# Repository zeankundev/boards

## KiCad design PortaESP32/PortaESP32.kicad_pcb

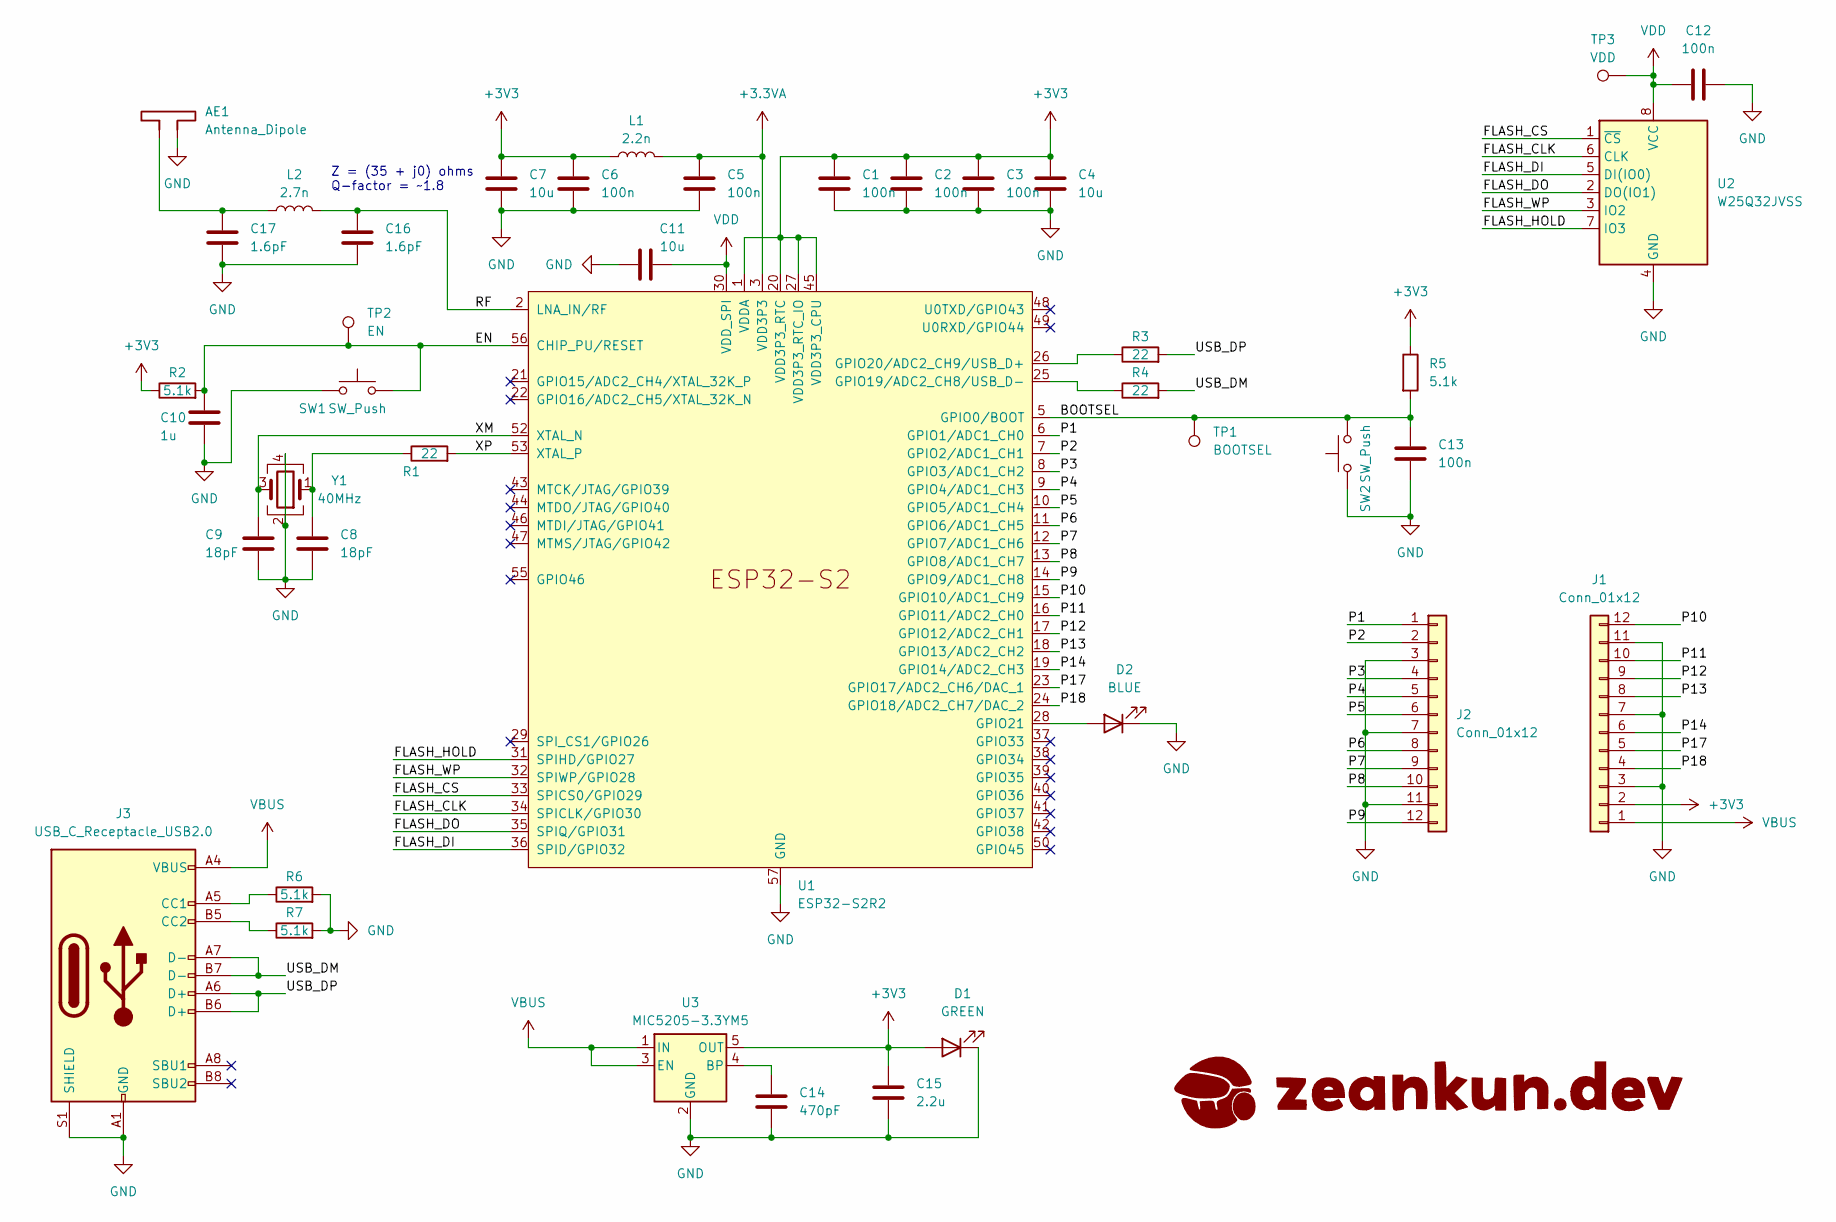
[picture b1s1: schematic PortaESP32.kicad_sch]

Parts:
AE1: Antenna_Dipole; Texas_SWRA117D_2.4GHz_Left
C1, C2, C3, C5, C6, C12, C13: 100n; C_0402_1005Metric
C4, C7, C11: 10u; C_0402_1005Metric
C8, C9: 18pF; C_0402_1005Metric
C10: 1u; C_0402_1005Metric
C14: 470pF; C_0402_1005Metric
C15: 2.2u; C_0402_1005Metric
C16, C17: 1.6pF; C_0402_1005Metric
D1: GREEN; LED_0402_1005Metric
D2: BLUE; LED_0402_1005Metric
J1, J2: Conn_01x12; Conn_01x12_2.54mm
J3: USB_C_Receptacle_USB2.0; USB_C_Receptacle_GCT_USB4105-xx-A_16P_TopMnt_Horizontal
L1: 2.2n; L_0402_1005Metric
L2: 2.7n; L_0402_1005Metric
R1, R3, R4: 22; R_0402_1005Metric
R2, R5, R6, R7: 5.1k; R_0402_1005Metric
SW1, SW2: SW_Push; SW_Push_1P1T_NO_Vertical_Wuerth_434133025816
TP1: BOOTSEL; TestPoint_Pad_D1.0mm
TP2: EN; TestPoint_Pad_D1.0mm
TP3: VDD; TestPoint_Pad_D1.0mm
U1: ESP32-S2R2; QFN-56-1EP_7x7mm_P0.4mm_EP4x4mm
U2: W25Q32JVSS; SOIC-8_5.23x5.23mm_P1.27mm
U3: MIC5205-3.3YM5; SOT-23-5
Y1: 40MHz; Crystal_SMD_3225-4Pin_3.2x2.5mm

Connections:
+3.3VA: C5.1, L1.2, U1.3 (VDD3P3), U1.4 (VDD3P3)
+3V3: C1.1, C2.1, C3.1, C4.1, C6.1, C7.1, C15.1, D1.2 (A), J1.2, L1.1, R2.1, R5.1, U1.1 (VDDA), U1.20 (VDD3P3_RTC), U1.27 (VDD3P3_RTC_IO), U1.45 (VDD3P3_CPU), U1.51 (VDDA), U1.54 (VDDA), U3.5 (OUT)
/BOOTSEL: C13.1, R5.2, SW2.2, TP1.1, U1.5 (GPIO0/BOOT)
/EN: C10.1, R2.2, SW1.2, TP2.1, U1.56 (CHIP_PU/RESET)
/FLASH_CLK: U1.34 (SPICLK/GPIO30), U2.6 (CLK)
/FLASH_CS: U1.33 (SPICS0/GPIO29), U2.1 (~CS)
/FLASH_DI: U1.36 (SPID/GPIO32), U2.5 (DI(IO0))
/FLASH_DO: U1.35 (SPIQ/GPIO31), U2.2 (DO(IO1))
/FLASH_HOLD: U1.31 (SPIHD/GPIO27), U2.7 (IO3)
/FLASH_WP: U1.32 (SPIWP/GPIO28), U2.3 (IO2)
/P1: J2.1, U1.6 (GPIO1/ADC1_CH0)
/P2: J2.2, U1.7 (GPIO2/ADC1_CH1)
/P3: J2.4, U1.8 (GPIO3/ADC1_CH2)
/P4: J2.5, U1.9 (GPIO4/ADC1_CH3)
/P5: J2.6, U1.10 (GPIO5/ADC1_CH4)
/P6: J2.8, U1.11 (GPIO6/ADC1_CH5)
/P7: J2.9, U1.12 (GPIO7/ADC1_CH6)
/P8: J2.10, U1.13 (GPIO8/ADC1_CH7)
/P9: J2.12, U1.14 (GPIO9/ADC1_CH8)
/P10: J1.12, U1.15 (GPIO10/ADC1_CH9)
/P11: J1.10, U1.16 (GPIO11/ADC2_CH0)
/P12: J1.9, U1.17 (GPIO12/ADC2_CH1)
/P13: J1.8, U1.18 (GPIO13/ADC2_CH2)
/P14: J1.6, U1.19 (GPIO14/ADC2_CH3)
/P17: J1.5, U1.23 (GPIO17/ADC2_CH6/DAC_1)
/P18: J1.4, U1.24 (GPIO18/ADC2_CH7/DAC_2)
/RF: C16.1, L2.2, U1.2 (LNA_IN/RF)
/USB_DM: J3.A7 (D-), J3.B7 (D-), R4.2
/USB_DP: J3.A6 (D+), J3.B6 (D+), R3.2
/XM: C9.1, U1.52 (XTAL_N), Y1.3
/XP: R1.2, U1.53 (XTAL_P)
GND: AE1.2, C1.2, C2.2, C3.2, C4.2, C5.2, C6.2, C7.2, C8.2, C9.2, C10.2, C11.1, C12.2, C13.2, C14.2, C15.2, C16.2, C17.2, D1.1 (K), D2.1 (K), J1.3, J1.7, J1.11, J2.3, J2.7, J2.11, J3.A1 (GND), J3.A12 (GND), J3.B1 (GND), J3.B12 (GND), J3.S1 (SHIELD), R6.2, R7.2, SW1.1, SW2.1, U1.57 (GND), U2.4 (GND), U3.2 (GND), Y1.2, Y1.4
unnamed: AE1.1, C17.1, L2.1
unnamed: C8.1, R1.1, Y1.1
unnamed: D2.2 (A), U1.28 (GPIO21)
unnamed: J3.A5 (CC1), R6.1
unnamed: J3.B5 (CC2), R7.1
unnamed: R4.1, U1.25 (GPIO19/ADC2_CH8/USB_D-)
unnamed: R3.1, U1.26 (GPIO20/ADC2_CH9/USB_D+)
unnamed: C14.1, U3.4 (BP)
VBUS: J1.1, J3.A4 (VBUS), J3.A9 (VBUS), J3.B4 (VBUS), J3.B9 (VBUS), U3.1 (IN), U3.3 (EN)
VDD: C11.2, C12.1, TP3.1, U1.30 (VDD_SPI), U2.8 (VCC)

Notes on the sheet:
Z = (35 + j0) ohms Q-factor = ~1.8

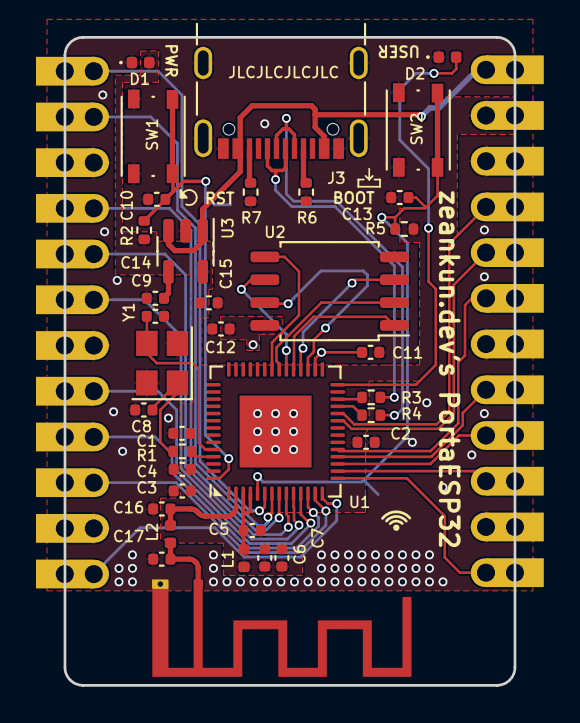
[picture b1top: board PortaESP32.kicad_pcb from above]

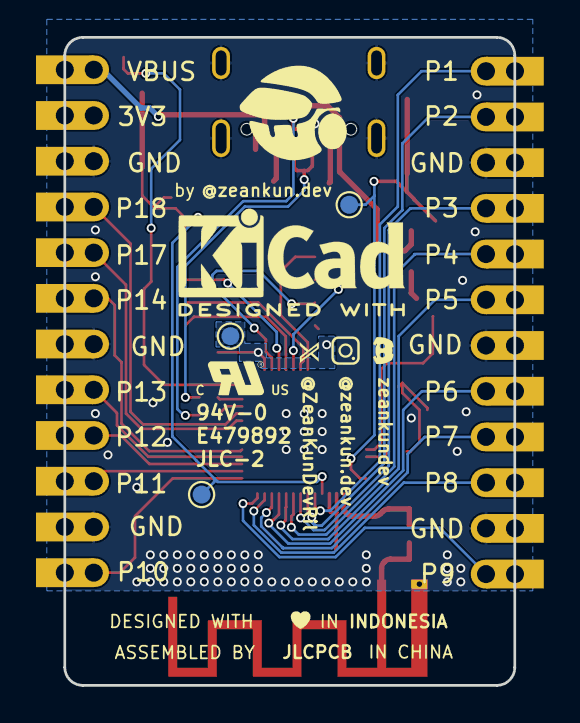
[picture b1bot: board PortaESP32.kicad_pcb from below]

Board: 2 copper layers, 25.0 x 36.0 mm, 41 parts (4 on the bottom side), 42 nets.

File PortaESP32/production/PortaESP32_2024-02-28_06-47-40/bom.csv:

Designator,Footprint,Quantity,Value,LCSC Part #
"C1, C12, C13, C2, C3, C5, C6",0402,7,100n,
C10,0402,1,1u,
"C11, C4, C7",0402,3,10u,
C14,0402,1,470pF,
C15,0402,1,2.2u,
"C16, C17",0402,2,1.6pF,
"C8, C9",0402,2,18pF,
D1,0402,1,GREEN,
D2,0402,1,BLUE,
J3,USB_C_Receptacle_GCT_USB4105-xx-A_16P_TopMnt_Horizontal,1,USB_C_Receptacle_USB2.0,
L1,0402,1,2.2n,
L2,0402,1,2.7n,
"R1, R3, R4",0402,3,22,
"R2, R5, R6, R7",0402,4,5.1k,
"SW1, SW2",SW_Push_1P1T_NO_Vertical_Wuerth_434133025816,2,SW_Push,
TP1,TestPoint_Pad_D1.0mm,1,BOOTSEL,
TP2,TestPoint_Pad_D1.0mm,1,EN,
TP3,TestPoint_Pad_D1.0mm,1,VDD,
U1,QFN-56-1EP_7x7mm_P0.4mm_EP4x4mm,1,ESP32-S2R2,
U2,SOIC-8_5.23x5.23mm_P1.27mm,1,W25Q32JVSS,
U3,SOT-23-5,1,MIC5205-3.3YM5,
Y1,Crystal_SMD_3225-4Pin_3.2x2.5mm,1,40MHz,

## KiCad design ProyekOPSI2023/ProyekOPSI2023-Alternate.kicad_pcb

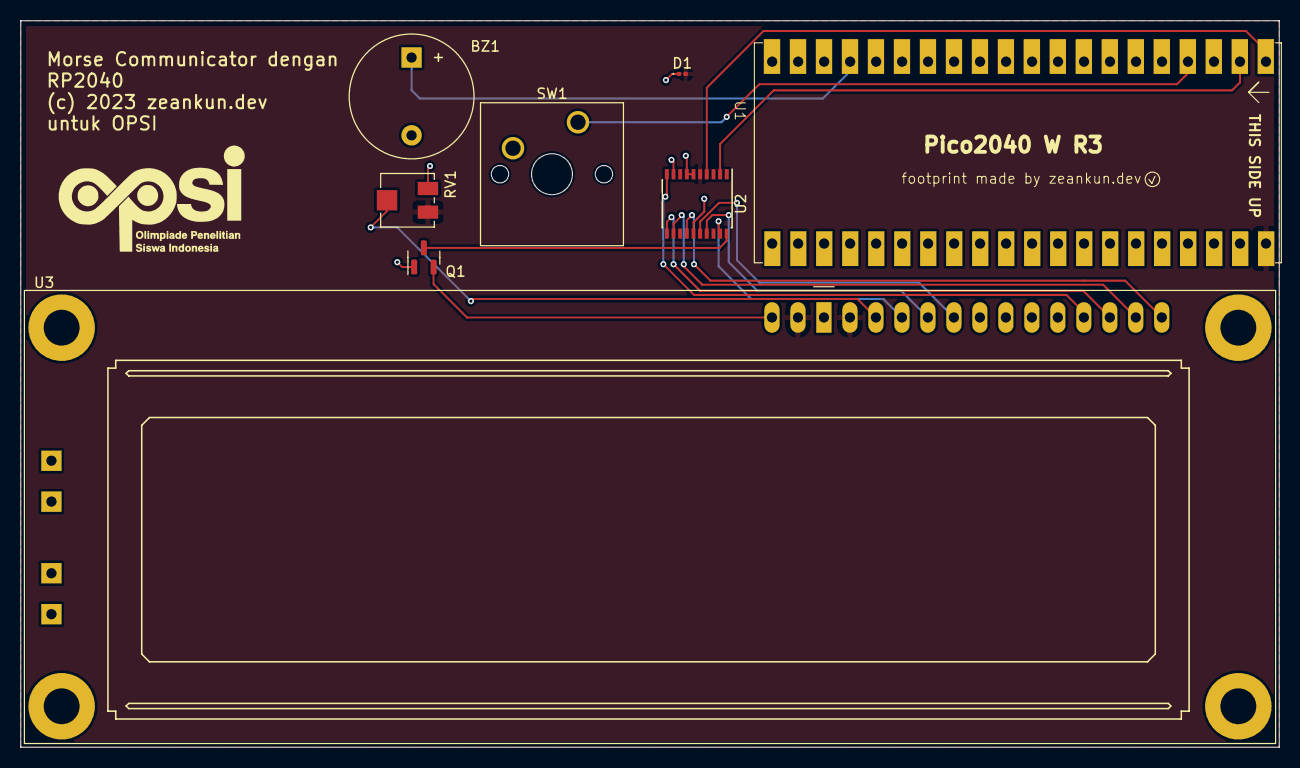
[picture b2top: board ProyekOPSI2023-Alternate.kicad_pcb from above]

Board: 2 copper layers, 123.0 x 71.0 mm, 8 parts (0 on the bottom side), 16 nets.

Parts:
BZ1: Buzzer; Buzzer_12x9.5RM7.6
D1: BLUE; LED_0201_0603Metric
Q1: BF545A; SOT-23
RV1: R_Potentiometer; Potentiometer_Vishay_TS53YJ_Vertical
SW1: SW_Push; SW_Cherry_MX_1.00u_PCB
U1: Pico2040 W R3; Pico2040-W-R3
U2: PCF8574ATS; SSOP-20_4.4x6.5mm_P0.65mm
U3: LCD-016N002L

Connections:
/B4: U2.10 (P0), U3.11 (DB4)
/B5: U2.11 (P1), U3.12 (DB5)
/B6: U2.12 (P2), U3.13 (DB6)
/B7: U2.14 (P3), U3.14 (DB7)
/E: U2.16 (P4), U3.6 (E)
/K: Q1.2 (D), U3.16 (K)
/K_SW: Q1.3 (G), U2.20 (P7)
/LCD_SCL: U1.2 (P1), U2.2 (SCL)
/LCD_SDA: U1.1 (P0), U2.4 (SDA)
/MORSE_INPUT: SW1.1, U1.4 (P2)
/RS: U2.19 (P6), U3.4 (RS)
/RW: U2.17 (P5), U3.5 (R/~W)
GND: BZ1.2 (+), D1.1 (K), Q1.1 (S), RV1.1, SW1.2, U1.3 (GND), U1.8 (GND), U1.13 (GND), U1.18 (GND), U1.23 (GND), U1.28 (GND), U1.33 (GND), U1.38 (GND), U2.6 (A0), U2.7 (A1), U2.9 (A2), U2.15 (VSS), U3.1 (VSS)
unnamed: BZ1.1 (-), U1.17 (P13)
unnamed: RV1.2, U3.3 (VO)
VBUS: D1.2 (A), RV1.3, U1.40 (VBUS(5V)), U2.5 (VDD), U3.2 (VDD), U3.15 (A/VEE)

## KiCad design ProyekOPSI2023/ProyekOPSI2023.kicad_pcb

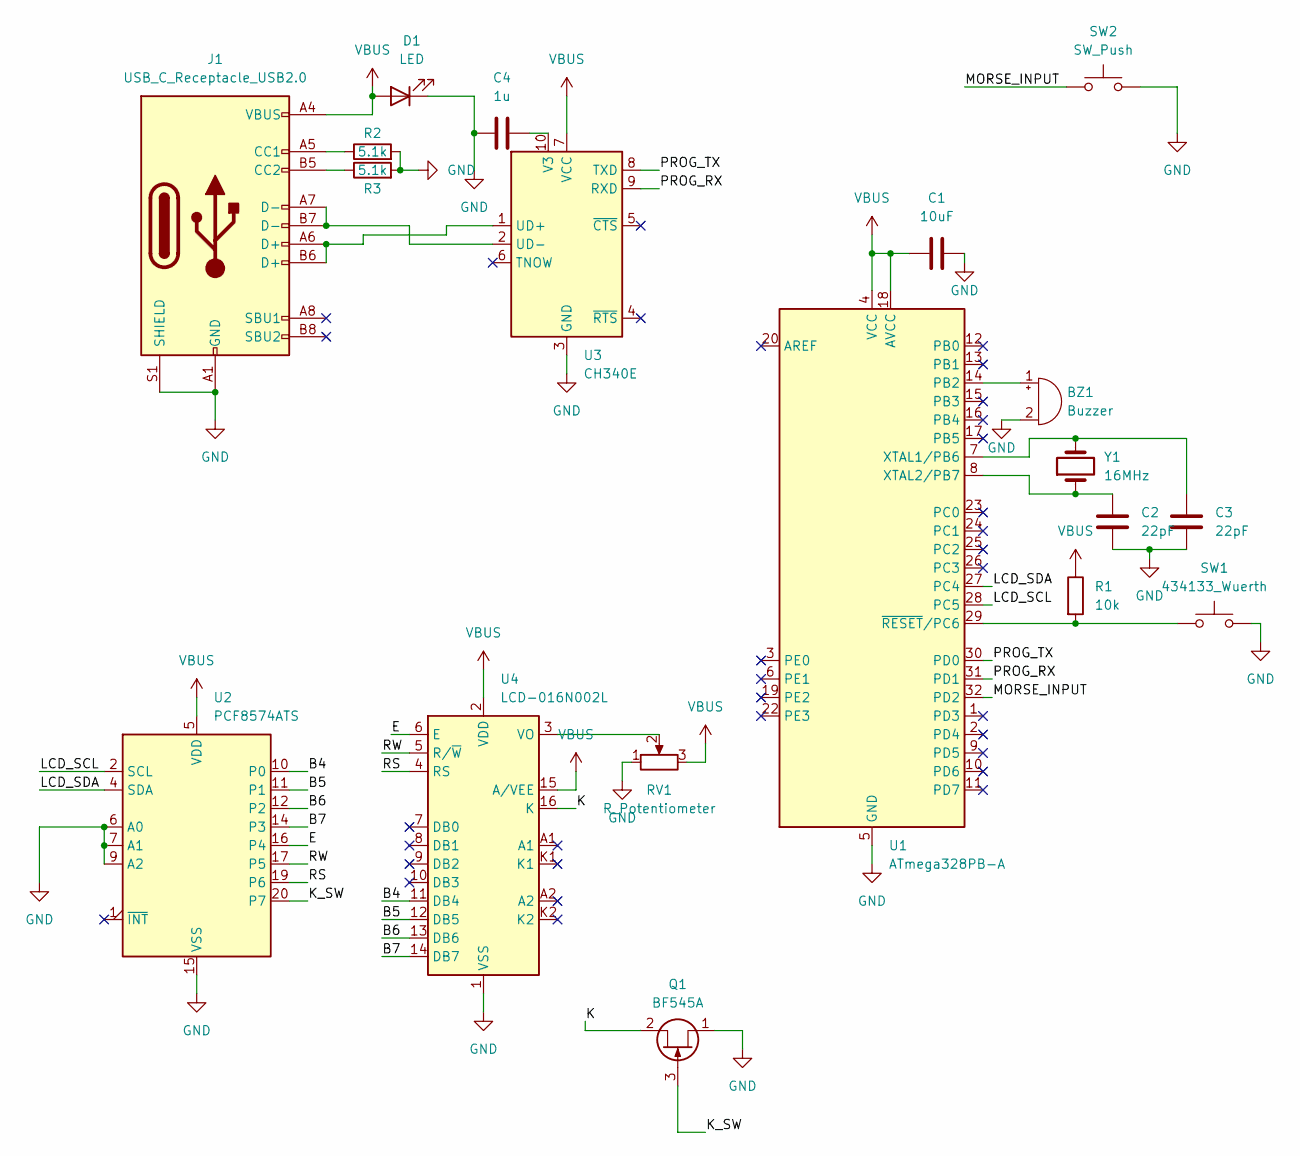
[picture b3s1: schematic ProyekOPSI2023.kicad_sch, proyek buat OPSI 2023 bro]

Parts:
BZ1: Buzzer; Buzzer_12x9.5RM7.6
C1: 10uF; C_0201_0603Metric
C2, C3: 22pF; C_0201_0603Metric
C4: 1u; C_0201_0603Metric
D1: LED; LED_0201_0603Metric
J1: USB_C_Receptacle_USB2.0; USB_C_Receptacle_G-Switch_GT-USB-7010ASV
Q1: BF545A; SOT-23
R1: 10k; R_0201_0603Metric
R2, R3: 5.1k; R_0201_0603Metric
RV1: R_Potentiometer; Potentiometer_Vishay_TS53YJ_Vertical
SW1: 434133_Wuerth; SW_Push_1P1T_NO_Vertical_Wuerth_434133025816
SW2: SW_Push; SW_Cherry_MX_1.00u_PCB
U1: ATmega328PB-A; TQFP-32_7x7mm_P0.8mm
U2: PCF8574ATS; SSOP-20_4.4x6.5mm_P0.65mm
U3: CH340E; MSOP-10_3x3mm_P0.5mm
U4: LCD-016N002L
Y1: 16MHz; Crystal_SMD_0603-2Pin_6.0x3.5mm

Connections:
/B4: U2.10 (P0), U4.11 (DB4)
/B5: U2.11 (P1), U4.12 (DB5)
/B6: U2.12 (P2), U4.13 (DB6)
/B7: U2.14 (P3), U4.14 (DB7)
/E: U2.16 (P4), U4.6 (E)
/K: Q1.2 (D), U4.16 (K)
/K_SW: Q1.3 (G), U2.20 (P7)
/LCD_SCL: U1.28 (PC5), U2.2 (SCL)
/LCD_SDA: U1.27 (PC4), U2.4 (SDA)
/MORSE_INPUT: SW2.1, U1.32 (PD2)
/PROG_RX: U1.31 (PD1), U3.9 (RXD)
/PROG_TX: U1.30 (PD0), U3.8 (TXD)
/RS: U2.19 (P6), U4.4 (RS)
/RW: U2.17 (P5), U4.5 (R/~W)
GND: BZ1.2 (+), C1.2, C2.2, C3.2, C4.1, D1.1 (K), J1.A1 (GND), J1.A12 (GND), J1.B1 (GND), J1.B12 (GND), J1.S1 (SHIELD), Q1.1 (S), R2.2, R3.2, RV1.1, SW1.2, SW2.2, U1.5 (GND), U1.21 (GND), U2.6 (A0), U2.7 (A1), U2.9 (A2), U2.15 (VSS), U3.3 (GND), U4.1 (VSS)
unnamed: BZ1.1 (-), U1.14 (PB2)
unnamed: J1.A5 (CC1), R2.1
unnamed: J1.B5 (CC2), R3.1
unnamed: C3.1, U1.7 (XTAL1/PB6), Y1.2
unnamed: C2.1, U1.8 (XTAL2/PB7), Y1.1
unnamed: R1.2, SW1.1, U1.29 (~RESET/PC6)
unnamed: J1.A6 (D+), J1.B6 (D+), U3.1 (UD+)
unnamed: J1.A7 (D-), J1.B7 (D-), U3.2 (UD-)
unnamed: C4.2, U3.10 (V3)
unnamed: RV1.2, U4.3 (VO)
VBUS: C1.1, D1.2 (A), J1.A4 (VBUS), J1.A9 (VBUS), J1.B4 (VBUS), J1.B9 (VBUS), R1.1, RV1.3, U1.4 (VCC), U1.18 (AVCC), U2.5 (VDD), U3.7 (VCC), U4.2 (VDD), U4.15 (A/VEE)

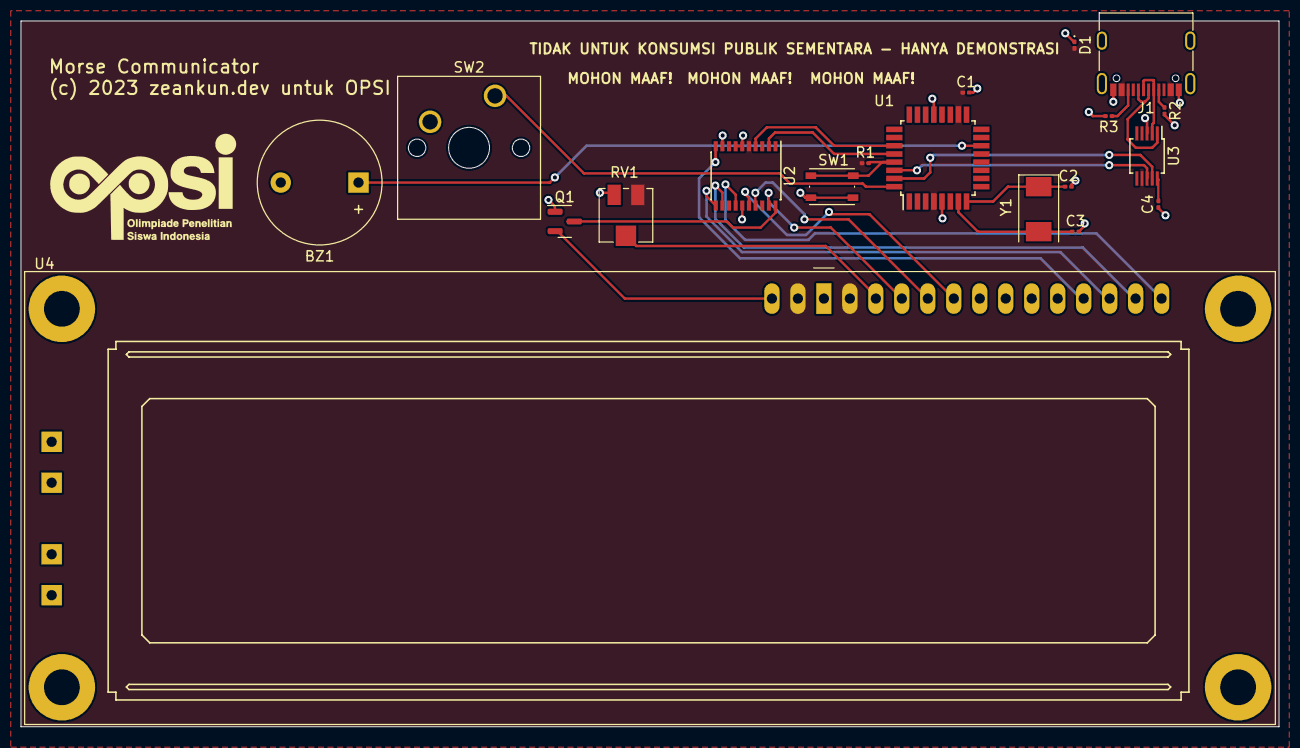
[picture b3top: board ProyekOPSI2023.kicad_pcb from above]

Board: 2 copper layers, 123.0 x 69.0 mm, 19 parts (0 on the bottom side), 26 nets.

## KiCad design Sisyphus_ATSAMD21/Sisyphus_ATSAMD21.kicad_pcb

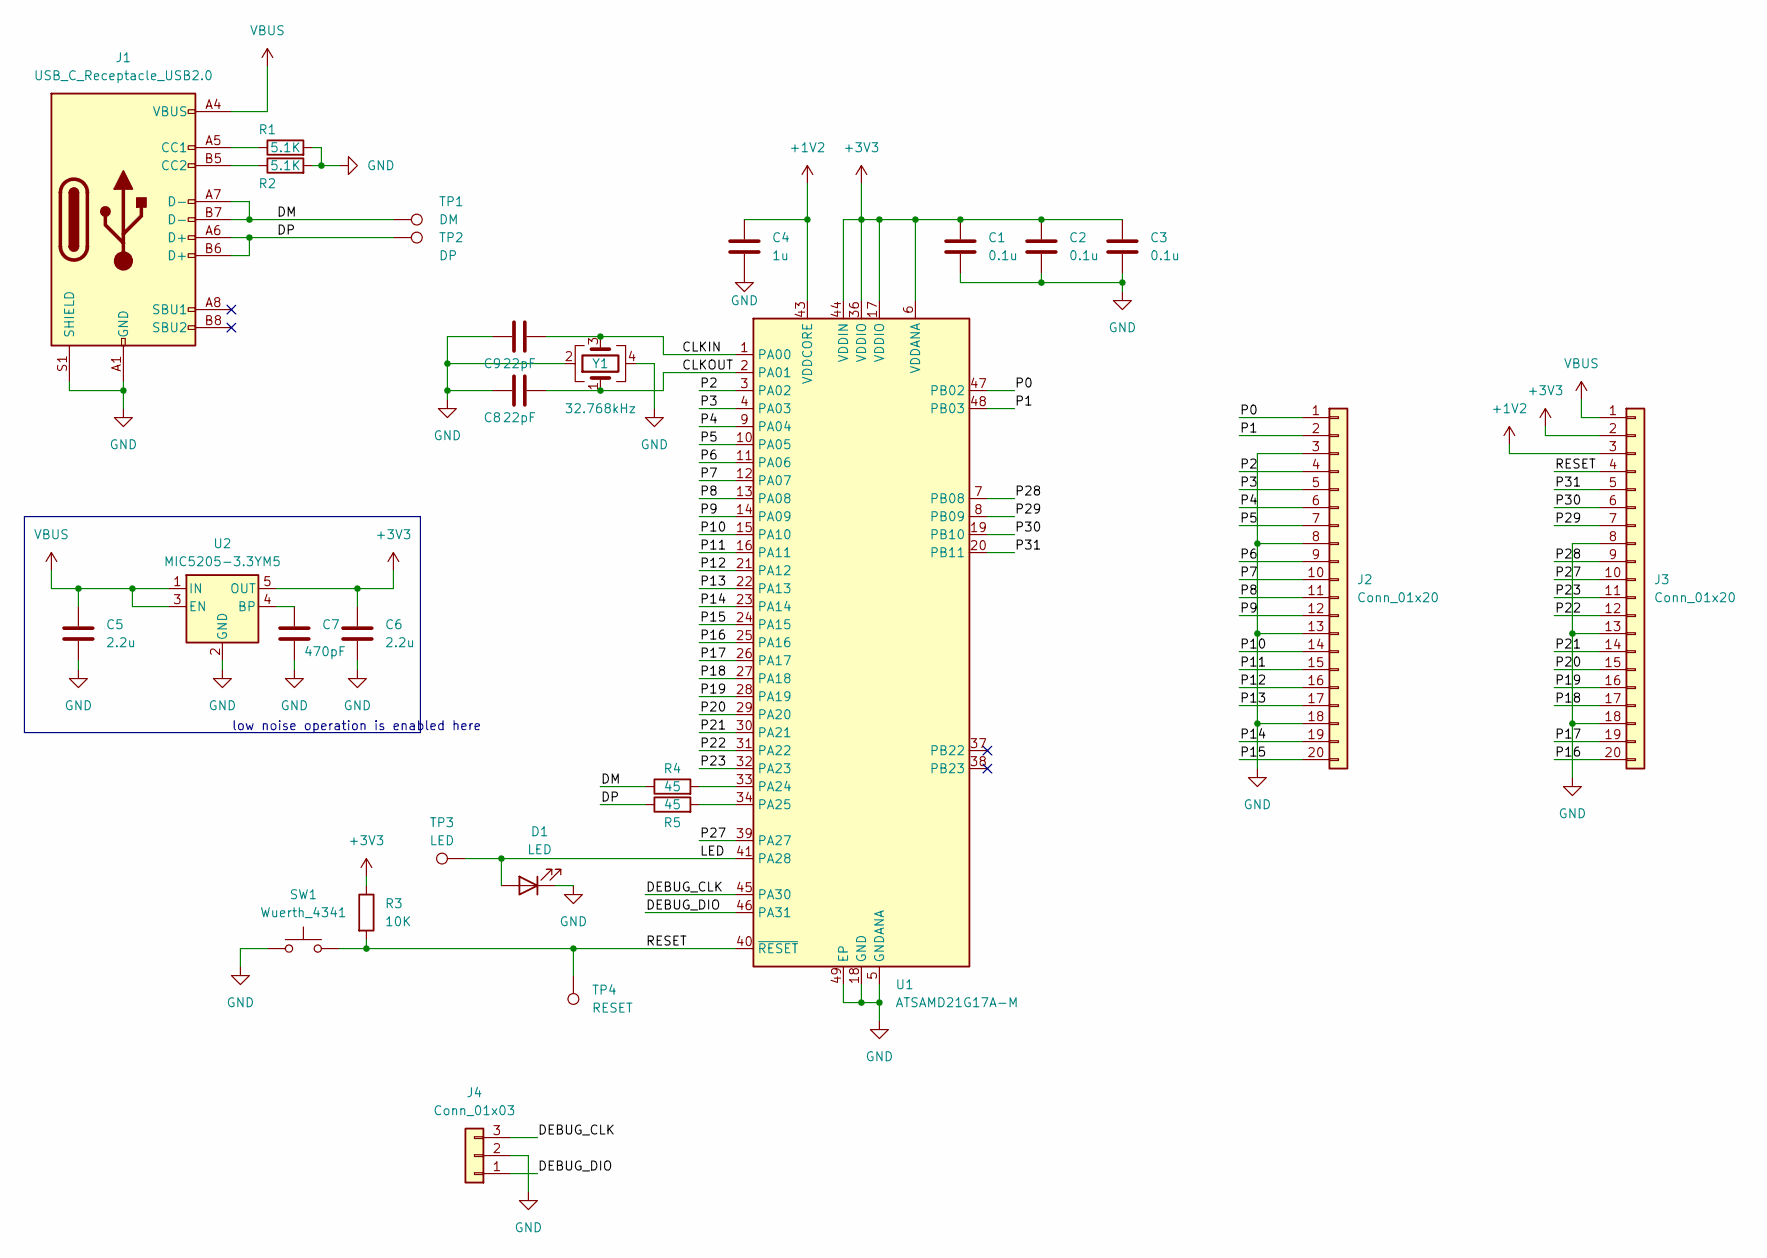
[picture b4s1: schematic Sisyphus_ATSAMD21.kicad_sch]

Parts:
C1, C2, C3: 0.1u; C_0201_0603Metric
C4: 1u; C_0201_0603Metric
C5, C6: 2.2u; C_0201_0603Metric
C7: 470pF; C_0201_0603Metric
C8, C9: 22pF; C_0201_0603Metric
D1: LED; LED_0201_0603Metric
J1: USB_C_Receptacle_USB2.0; USB_C_Receptacle_GCT_USB4105-xx-A_16P_TopMnt_Horizontal
J2, J3: Conn_01x20; Conn_01x20_2.54mm
J4: Conn_01x03; PinHeader_1x03_P2.54mm_Vertical
R1, R2: 5.1K; R_0201_0603Metric
R3: 10K; R_0201_0603Metric
R4, R5: 45; R_0201_0603Metric
SW1: Wuerth_4341; SW_Push_1P1T_NO_Vertical_Wuerth_434133025816
TP1: DM; TestPoint_Pad_D1.0mm
TP2: DP; TestPoint_Pad_D1.0mm
TP3: LED; TestPoint_Pad_D1.0mm
TP4: RESET; TestPoint_Pad_D1.0mm
U1: ATSAMD21G17A-M; QFN-48-1EP_7x7mm_P0.5mm_EP5.15x5.15mm
U2: MIC5205-3.3YM5; SOT-23-5
Y1: 32.768kHz; Crystal_SMD_2520-4Pin_2.5x2.0mm

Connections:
+1V2: C4.1, J3.3, U1.43 (VDDCORE)
+3V3: C1.1, C2.1, C3.1, C6.1, J3.2, R3.1, U1.6 (VDDANA), U1.17 (VDDIO), U1.36 (VDDIO), U1.44 (VDDIN), U2.5 (OUT)
/CLKIN: C9.2, U1.1 (PA00), Y1.3
/CLKOUT: C8.2, U1.2 (PA01), Y1.1
/DEBUG_CLK: J4.3, U1.45 (PA30)
/DEBUG_DIO: J4.1, U1.46 (PA31)
/DM: J1.A7 (D-), J1.B7 (D-), R4.1, TP1.1
/DP: J1.A6 (D+), J1.B6 (D+), R5.1, TP2.1
/LED: D1.2 (A), TP3.1, U1.41 (PA28)
/P0: J2.1, U1.47 (PB02)
/P1: J2.2, U1.48 (PB03)
/P2: J2.4, U1.3 (PA02)
/P3: J2.5, U1.4 (PA03)
/P4: J2.6, U1.9 (PA04)
/P5: J2.7, U1.10 (PA05)
/P6: J2.9, U1.11 (PA06)
/P7: J2.10, U1.12 (PA07)
/P8: J2.11, U1.13 (PA08)
/P9: J2.12, U1.14 (PA09)
/P10: J2.14, U1.15 (PA10)
/P11: J2.15, U1.16 (PA11)
/P12: J2.16, U1.21 (PA12)
/P13: J2.17, U1.22 (PA13)
/P14: J2.19, U1.23 (PA14)
/P15: J2.20, U1.24 (PA15)
/P16: J3.20, U1.25 (PA16)
/P17: J3.19, U1.26 (PA17)
/P18: J3.17, U1.27 (PA18)
/P19: J3.16, U1.28 (PA19)
/P20: J3.15, U1.29 (PA20)
/P21: J3.14, U1.30 (PA21)
/P22: J3.12, U1.31 (PA22)
/P23: J3.11, U1.32 (PA23)
/P27: J3.10, U1.39 (PA27)
/P28: J3.9, U1.7 (PB08)
/P29: J3.7, U1.8 (PB09)
/P30: J3.6, U1.19 (PB10)
/P31: J3.5, U1.20 (PB11)
/RESET: J3.4, R3.2, SW1.2, TP4.1, U1.40 (~RESET)
GND: C1.2, C2.2, C3.2, C4.2, C5.2, C6.2, C7.2, C8.1, C9.1, D1.1 (K), J1.A1 (GND), J1.A12 (GND), J1.B1 (GND), J1.B12 (GND), J1.S1 (SHIELD), J2.3, J2.8, J2.13, J2.18, J3.8, J3.13, J3.18, J4.2, R1.2, R2.2, SW1.1, U1.5 (GNDANA), U1.18 (GND), U1.35 (GND), U1.42 (GND), U1.49 (EP), U2.2 (GND), Y1.2, Y1.4
unnamed: J1.A5 (CC1), R1.1
unnamed: J1.B5 (CC2), R2.1
unnamed: R4.2, U1.33 (PA24)
unnamed: R5.2, U1.34 (PA25)
unnamed: C7.1, U2.4 (BP)
VBUS: C5.1, J1.A4 (VBUS), J1.A9 (VBUS), J1.B4 (VBUS), J1.B9 (VBUS), J3.1, U2.1 (IN), U2.3 (EN)

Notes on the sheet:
low noise operation is enabled here

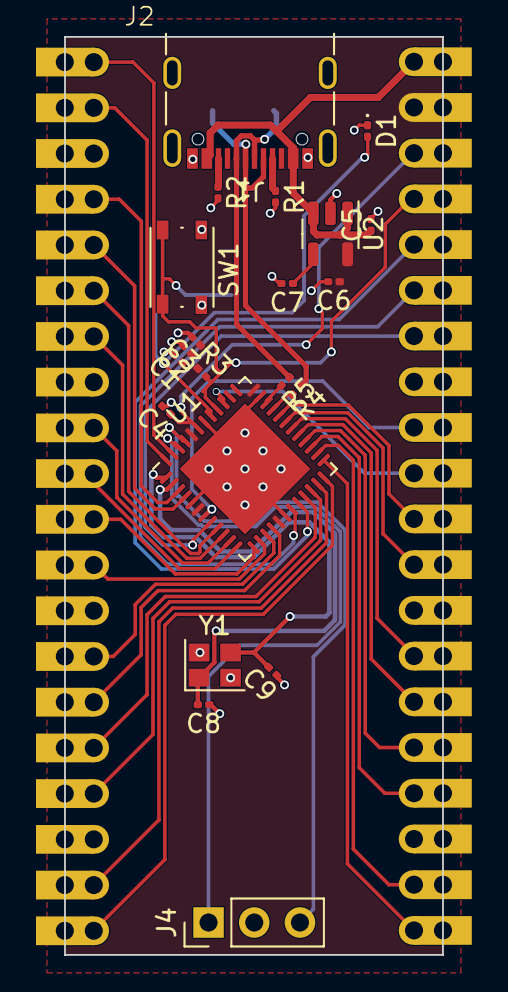
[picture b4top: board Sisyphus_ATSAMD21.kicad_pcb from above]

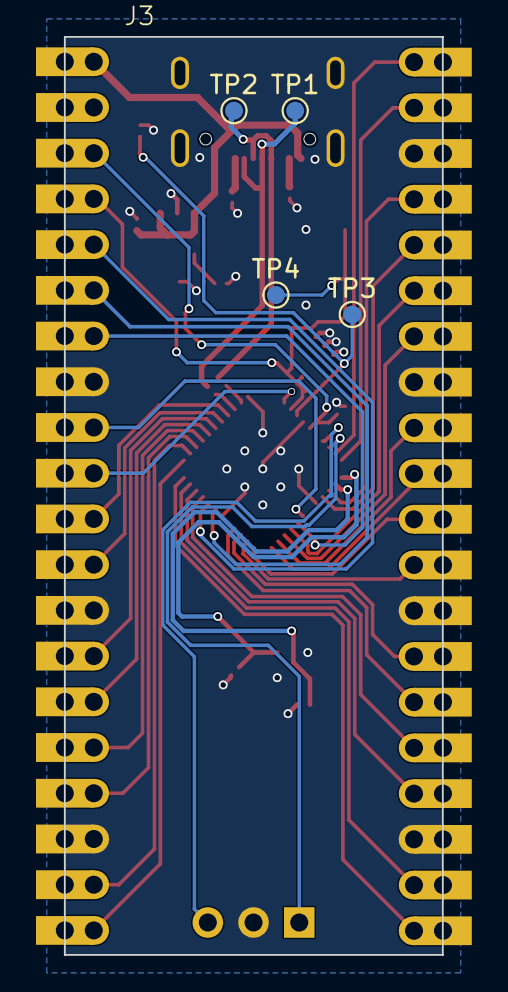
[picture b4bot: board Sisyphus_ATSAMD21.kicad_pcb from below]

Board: 2 copper layers, 21.0 x 51.0 mm, 27 parts (5 on the bottom side), 46 nets.

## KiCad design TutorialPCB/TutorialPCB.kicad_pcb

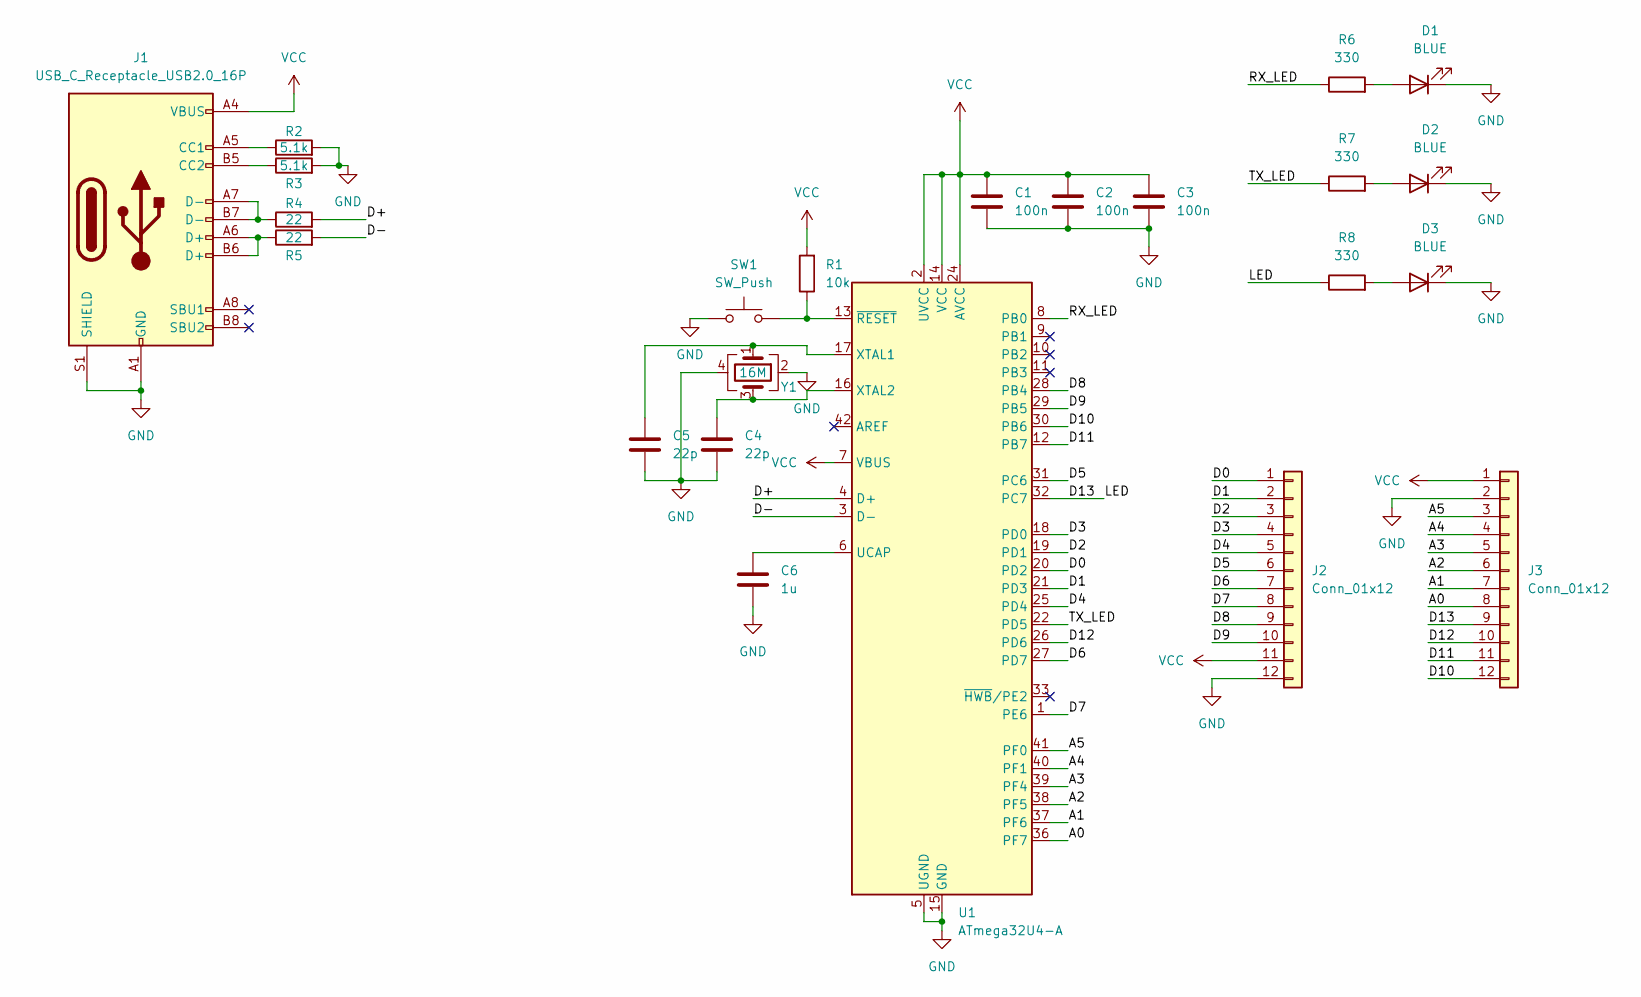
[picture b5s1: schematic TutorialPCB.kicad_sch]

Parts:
C1, C2, C3: 100n; C_0402_1005Metric
C4, C5: 22p; C_0402_1005Metric
C6: 1u; C_0402_1005Metric
D1, D2, D3: BLUE; LED_0402_1005Metric
J1: USB_C_Receptacle_USB2.0_16P; USB_C_Receptacle_GCT_USB4105-xx-A_16P_TopMnt_Horizontal
J2, J3: Conn_01x12; PinHeader_1x12_P2.54mm_Vertical
R1: 10k; R_0402_1005Metric
R2, R3: 5.1k; R_0402_1005Metric
R4, R5: 22; R_0402_1005Metric
R6, R7, R8: 330; R_0402_1005Metric
SW1: SW_Push; SW_Push_1P1T_NO_CK_KMR2
U1: ATmega32U4-A; TQFP-44_10x10mm_P0.8mm
Y1: 16M; Crystal_SMD_2520-4Pin_2.5x2.0mm

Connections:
/A0: J3.8, U1.36 (PF7)
/A1: J3.7, U1.37 (PF6)
/A2: J3.6, U1.38 (PF5)
/A3: J3.5, U1.39 (PF4)
/A4: J3.4, U1.40 (PF1)
/A5: J3.3, U1.41 (PF0)
/D0: J2.1, U1.20 (PD2)
/D1: J2.2, U1.21 (PD3)
/D2: J2.3, U1.19 (PD1)
/D3: J2.4, U1.18 (PD0)
/D4: J2.5, U1.25 (PD4)
/D5: J2.6, U1.31 (PC6)
/D6: J2.7, U1.27 (PD7)
/D7: J2.8, U1.1 (PE6)
/D8: J2.9, U1.28 (PB4)
/D9: J2.10, U1.29 (PB5)
/D10: J3.12, U1.30 (PB6)
/D11: J3.11, U1.12 (PB7)
/D12: J3.10, U1.26 (PD6)
/D13: J3.9, R8.1, U1.32 (PC7)
/D+: R4.2, U1.4 (D+)
/D-: R5.2, U1.3 (D-)
/RX_LED: R6.1, U1.8 (PB0)
/TX_LED: R7.1, U1.22 (PD5)
GND: C1.2, C2.2, C3.2, C4.2, C5.2, C6.2, D1.1 (K), D2.1 (K), D3.1 (K), J1.A1 (GND), J1.A12 (GND), J1.B1 (GND), J1.B12 (GND), J1.S1 (SHIELD), J2.12, J3.2, R2.2, R3.2, SW1.1, U1.5 (UGND), U1.15 (GND), U1.23 (GND), U1.35 (GND), U1.43 (GND), Y1.2, Y1.4
unnamed: D1.2 (A), R6.2
unnamed: D2.2 (A), R7.2
unnamed: D3.2 (A), R8.2
unnamed: J1.A5 (CC1), R2.1
unnamed: J1.B5 (CC2), R3.1
unnamed: J1.A6 (D+), J1.B6 (D+), R5.1
unnamed: J1.A7 (D-), J1.B7 (D-), R4.1
unnamed: C6.1, U1.6 (UCAP)
unnamed: C5.1, U1.17 (XTAL1), Y1.1
unnamed: C4.1, U1.16 (XTAL2), Y1.3
unnamed: R1.1, SW1.2, U1.13 (~RESET)
VCC: C1.1, C2.1, C3.1, J1.A4 (VBUS), J1.A9 (VBUS), J1.B4 (VBUS), J1.B9 (VBUS), J2.11, J3.1, R1.2, U1.2 (UVCC), U1.7 (VBUS), U1.14 (VCC), U1.24 (AVCC), U1.34 (VCC), U1.44 (AVCC)

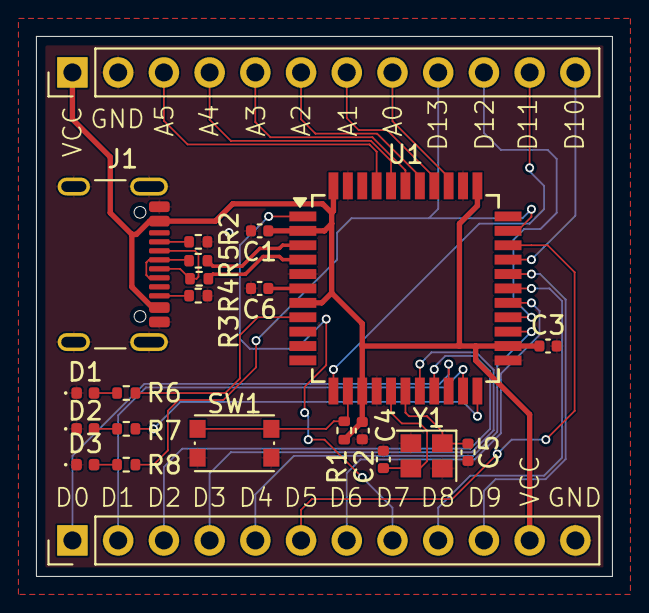
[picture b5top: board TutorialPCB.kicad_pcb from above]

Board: 2 copper layers, 32.0 x 30.0 mm, 23 parts (0 on the bottom side), 37 nets.

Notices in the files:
ProyekOPSI2023/ProyekOPSI2023-Alternate.kicad_pcb:
(c) 2023 zeankun.dev
ProyekOPSI2023/ProyekOPSI2023.kicad_pcb:
(c) 2023 zeankun.dev untuk OPSI
